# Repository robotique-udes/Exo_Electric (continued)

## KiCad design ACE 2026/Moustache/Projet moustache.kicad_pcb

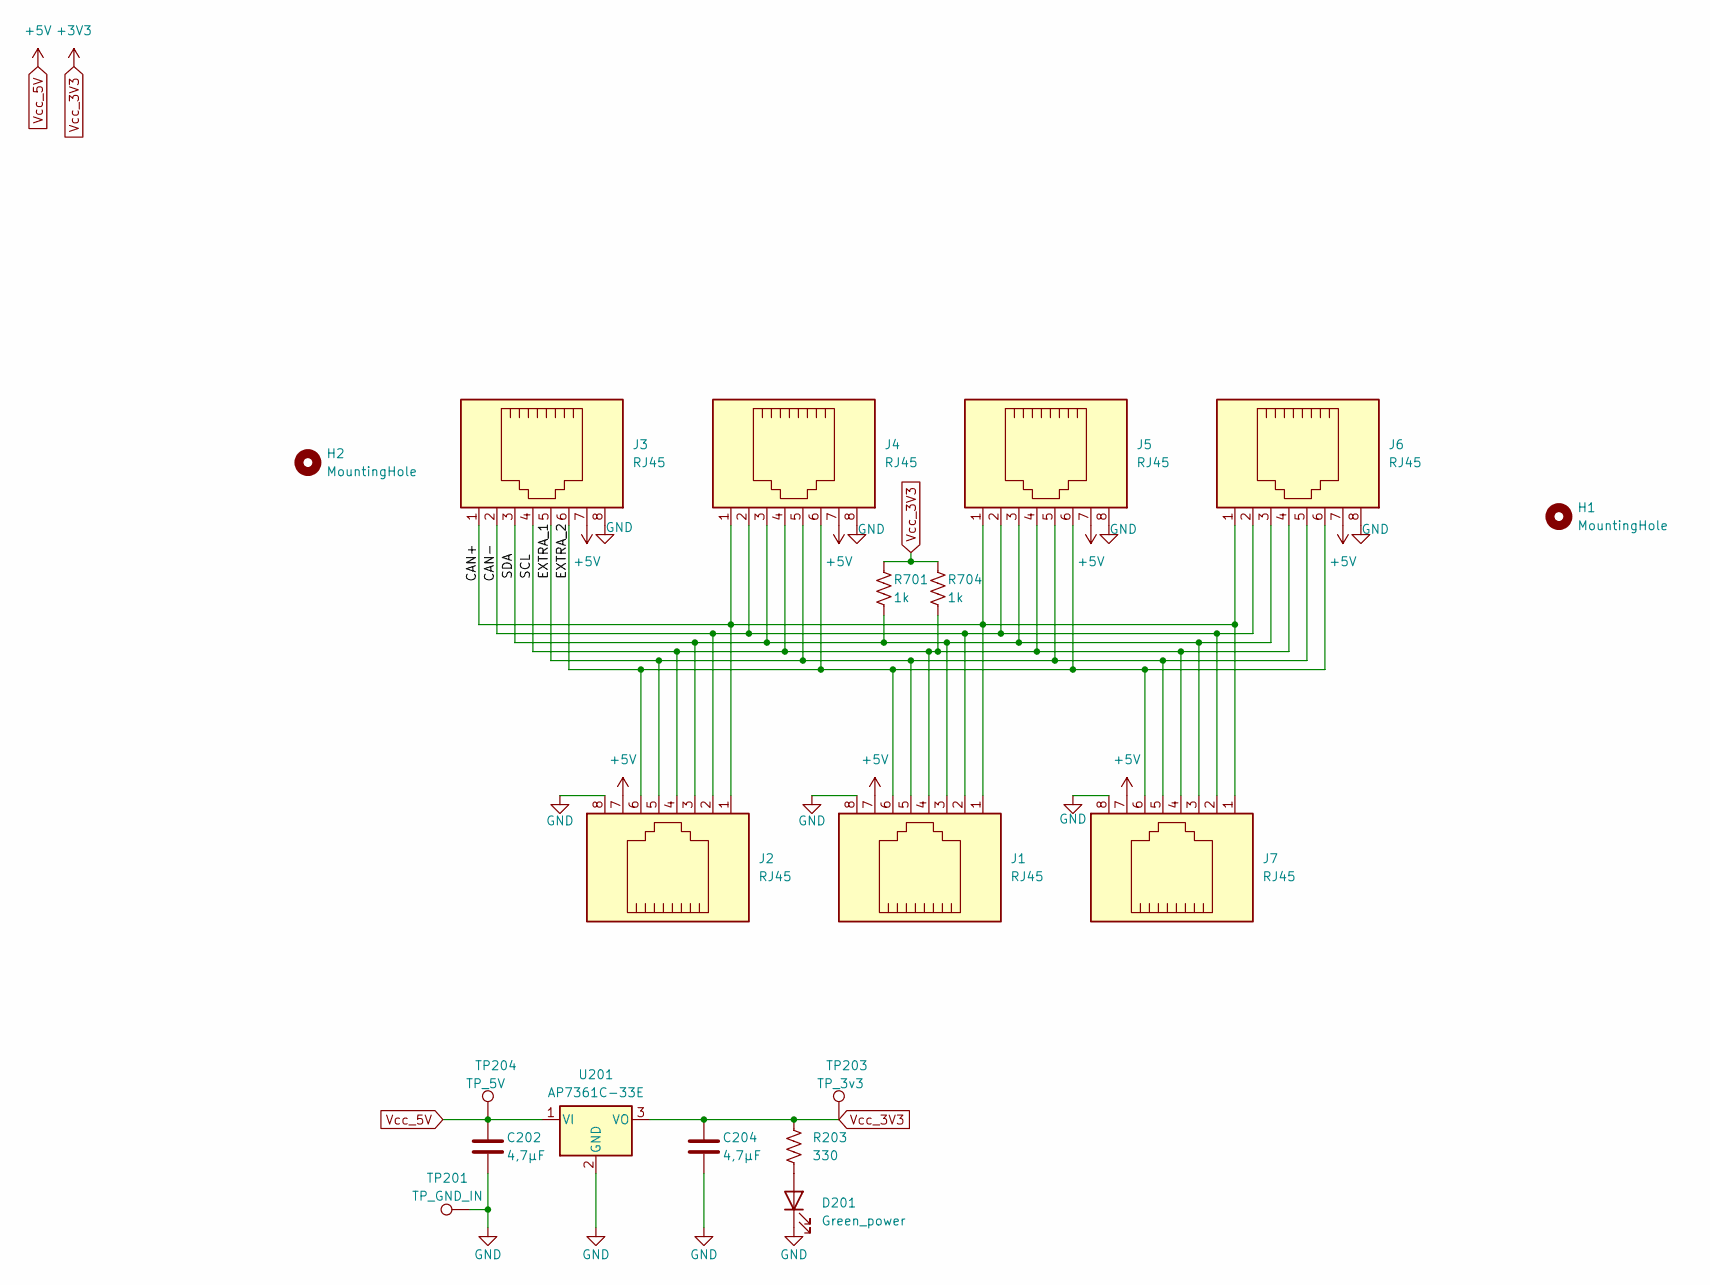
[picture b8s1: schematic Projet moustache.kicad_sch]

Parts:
C202, C204: 4,7µF; C_0805_2012Metric_Pad1.18x1.45mm_HandSolder
D201: Green_power; D_0805_2012Metric
H1, H2: MountingHole; MountingHole_3.2mm_M3
J1, J2, J3, J4, J5, J6, J7: RJ45; RJ45_Amphenol_54602-x08_Horizontal
R203: 330; R_0805_2012Metric_Pad1.20x1.40mm_HandSolder
R701, R704: 1k; R_0805_2012Metric_Pad1.20x1.40mm_HandSolder
TP201: TP_GND_IN; TestPoint_Pad_4.0x4.0mm
TP203: TP_3v3; TestPoint_Pad_D4.0mm
TP204: TP_5V; TestPoint_Pad_D4.0mm
U201: AP7361C-33E; SOT-223-3_TabPin2

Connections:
/CAN+: J1.1, J2.1, J3.1, J4.1, J5.1, J6.1, J7.1
/CAN-: J1.2, J2.2, J3.2, J4.2, J5.2, J6.2, J7.2
/EXTRA_1: J1.5, J2.5, J3.5, J4.5, J5.5, J6.5, J7.5
/EXTRA_2: J1.6, J2.6, J3.6, J4.6, J5.6, J6.6, J7.6
/SCL: J1.4, J2.4, J3.4, J4.4, J5.4, J6.4, J7.4, R704.2
/SDA: J1.3, J2.3, J3.3, J4.3, J5.3, J6.3, J7.3, R701.2
GND: C202.1, C204.1, D201.1 (K), J1.8, J2.8, J3.8, J4.8, J5.8, J6.8, J7.8, TP201.1, U201.2 (GND)
unnamed: D201.2 (A), R203.2
Vcc_3V3: C204.2, R203.1, R701.1, R704.1, TP203.1, U201.3 (VO)
Vcc_5V: C202.2, J1.7, J2.7, J3.7, J4.7, J5.7, J6.7, J7.7, TP204.1, U201.1 (VI)

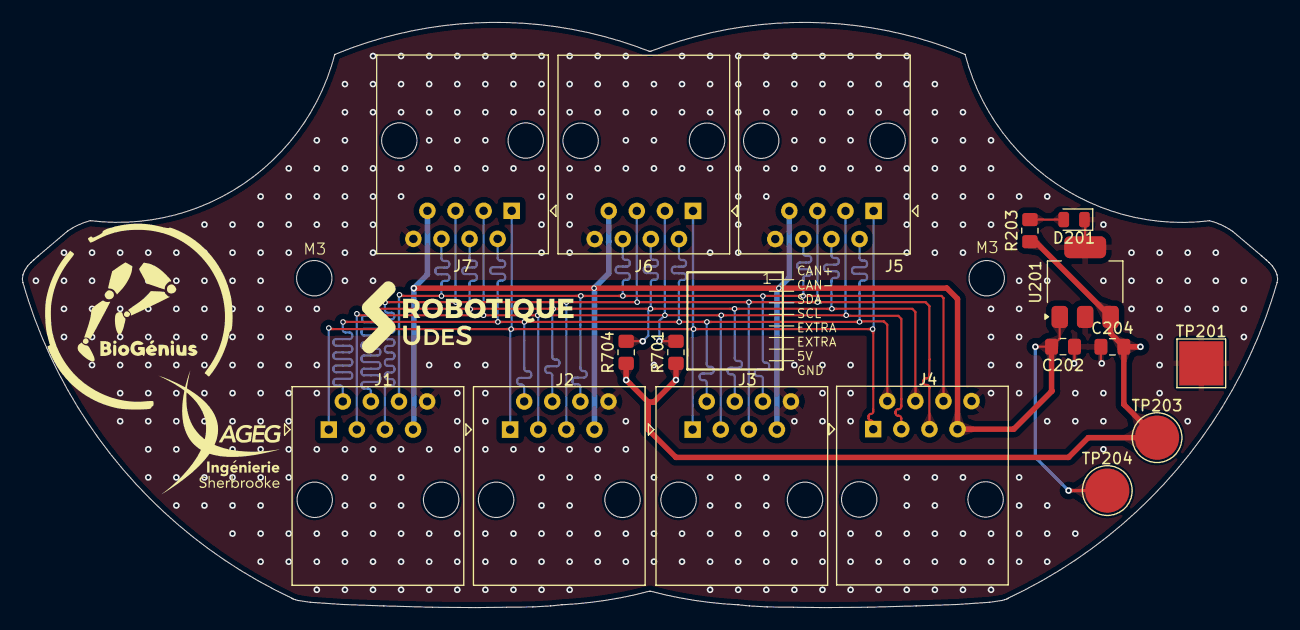
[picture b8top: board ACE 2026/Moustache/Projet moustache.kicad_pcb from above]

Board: 2 copper layers, 113.5 x 52.9 mm, 19 parts (0 on the bottom side), 10 nets.

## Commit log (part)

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2026-06-18 Add best practices for electrical design documentation
    This document outlines best practices for creating and reviewing electrical designs, including versioning conventions, component naming, and documentation requirements.
2026-06-23 Initial commit for the BIMU
2026-06-24 Correct minor mistake
2026-06-24 Avancement of different part of the schematic
    Add and reorganize numerous symbol definitions and annotations in Alimentation.kicad_sch: new TestPoint, LED, R_US/Resistor symbols, BAV99 diode, MountingHole, AP7361C-33E regulator, power/GND symbol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
